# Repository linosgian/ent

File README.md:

# Ent

## Ergogen generated split keyboard

This fork of [ergogen](https://github.com/linosgian/ergogen/tree/lgian/custom_footprints) is used, which contains all the custom footprints that appear on the board (holes, trackpad, elite-c etc)

left | right
-|-
 | 

## Features

* Support for a [cirque](https://keycapsss.com/keyboard-parts/parts/211/glidepoint-cirque-trackpad-tm040040-tm035035?c=11) and [Azoteq](https://keycapsss.com/keyboard-parts/parts/247/azoteq-proxsense-i2c-touch-sensor-module/capacitive-trackpad) trackpads on the right side (solderable jumpers)
* Support for a rotary encoder on the left side (solderable jumpers)
* Uses elite-c (or equivalent like puchi-c) so more io pins are available
* No diodes (less complexity during soldering)
* Reversible
* Only supports choc v1

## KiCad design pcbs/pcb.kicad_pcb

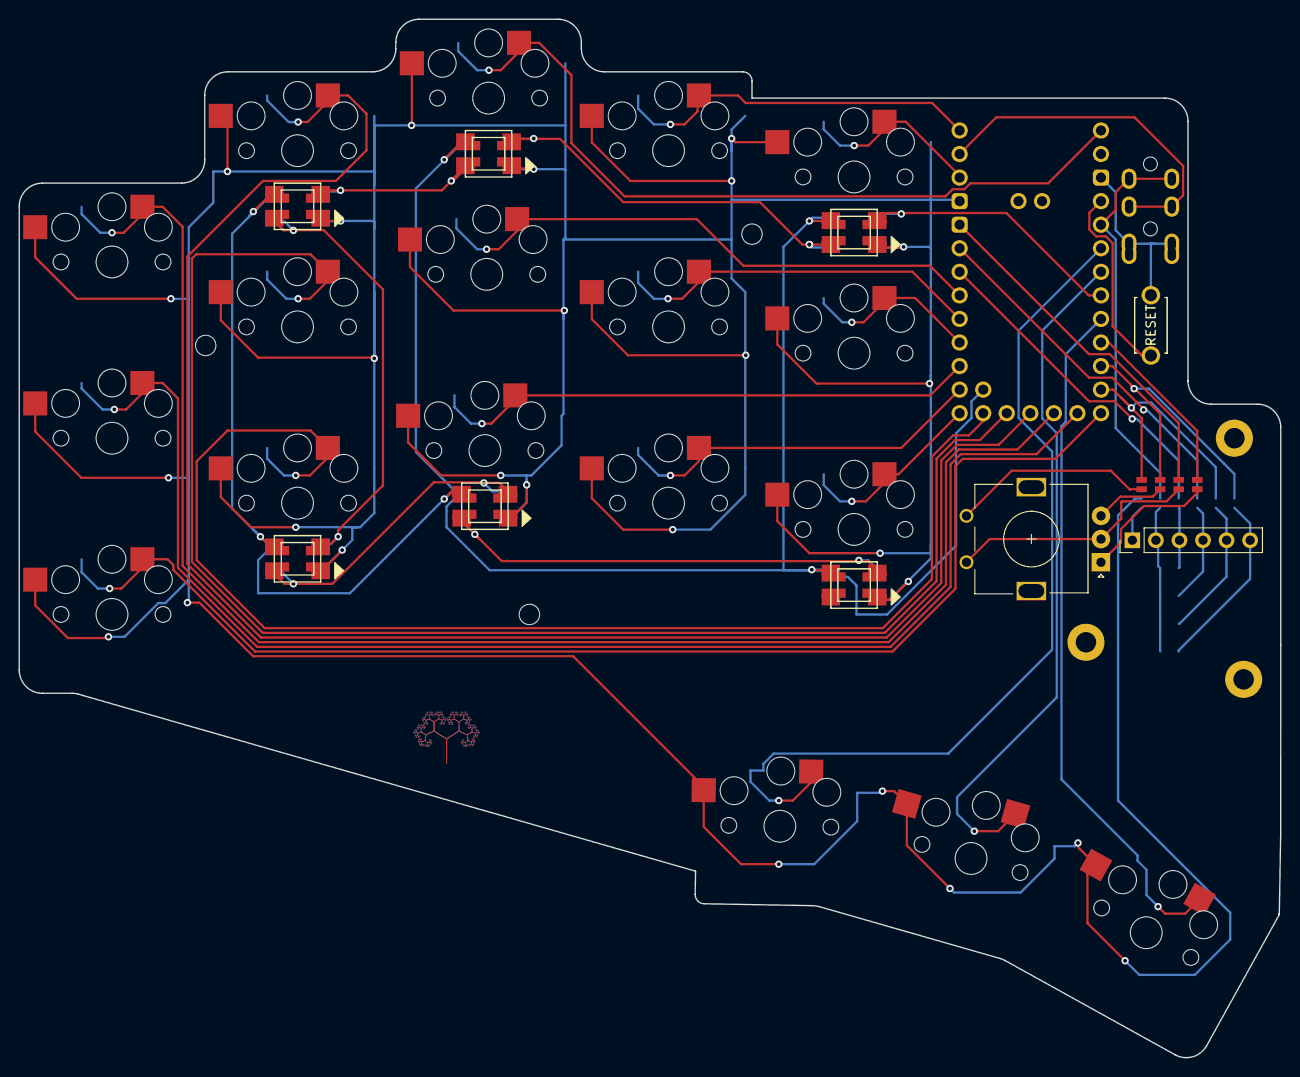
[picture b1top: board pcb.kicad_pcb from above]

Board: 2 copper layers, 136.0 x 112.0 mm, 50 parts (0 on the bottom side), 39 nets.

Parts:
J1, J2, J3, J4, J5, J6, J7, J8, J9, J10: Jumper
LED1, LED2, LED3, LED4, LED5, LED6, LED7, LED8, LED9, LED10, LED11, LED12: WS2812B
MCU1: Elite-C; Helios
ROT1: rotary_encoder
S1, S2, S3, S4, S5, S6, S7, S8, S9, S10, S11, S12, S13, S14, S15, S16, S17, S18: PG1350
TRRS1: TRRS-PJ-320A-dual
_1: ResetSW
_2, _3, _4: MountingHole_2.2mm_M2_Pad_Via
_5, _6, _7: MountingHole_2.2mm_M2

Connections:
A0: MCU1.23, S18.1
A1: LED5.4, LED5.44, LED11.4, LED11.44, MCU1.24
A2: MCU1.25, S17.1
A3: MCU1.26, S16.1
GND: J3.2, J5.2, LED1.3, LED1.33, LED2.3, LED2.33, LED3.3, LED3.33, LED4.3, LED4.33, LED5.3, LED5.33, LED6.3, LED6.33, LED7.3, LED7.33, LED8.3, LED8.33, LED9.3, LED9.33, LED10.3, LED10.33, LED11.3, LED11.33, LED12.3, LED12.33, MCU1.4, MCU1.5, MCU1.29, S1.2, S2.2, S3.2, S4.2, S5.2, S6.2, S7.2, S8.2, S9.2, S10.2, S11.2, S12.2, S13.2, S14.2, S15.2, S16.2, S17.2, S18.2, TRRS1.1, TRRS1.2, _1.2
IO2: J8.2, MCU1.6
IO3: J7.2, MCU1.7
IO4: MCU1.8, S8.1
IO5: MCU1.9, S11.1
IO6: MCU1.10, S14.1
IO7: MCU1.11, S7.1
IO8: MCU1.12, S10.1
IO9: MCU1.13, S13.1
IO10: MCU1.1, S12.1
IO11: MCU1.31, S9.1
IO12: MCU1.14, S4.1
IO13: MCU1.15, S5.1
IO14: MCU1.16, S6.1
IO15: MCU1.17, S3.1
IO16: MCU1.18, S2.1
IO20: J2.2, J10.2, MCU1.21
IO21: MCU1.19, S1.1
IO22: J4.2, MCU1.22
IO23: J1.2, J9.2, MCU1.20
NAN: LED6.2, LED6.22, LED12.2, LED12.22
O2: J1.1, ROT1.2
O3: J4.1, ROT1.A
O4: J3.1, ROT1.1, ROT1.C
O5: J2.1, ROT1.B
RGB: LED1.1, LED1.11, LED2.1, LED2.11, LED3.1, LED3.11, LED4.1, LED4.11, LED5.1, LED5.11, LED6.1, LED6.11, LED7.1, LED7.11, LED8.1, LED8.11, LED9.1, LED9.11, LED10.1, LED10.11, LED11.1, LED11.11, LED12.1, LED12.11, MCU1.32
RGB1: LED3.4, LED3.44, LED5.2, LED5.22, LED9.4, LED9.44, LED11.2, LED11.22
RGB2: LED1.4, LED1.44, LED3.2, LED3.22, LED7.4, LED7.44, LED9.2, LED9.22
RGB3: LED1.2, LED1.22, LED2.4, LED2.44, LED7.2, LED7.22, LED8.4, LED8.44
RGB4: LED2.2, LED2.22, LED4.4, LED4.44, LED8.2, LED8.22, LED10.4, LED10.44
RGB5: LED4.2, LED4.22, LED6.4, LED6.44, LED10.2, LED10.22, LED12.4, LED12.44
RST: MCU1.28, _1.1
RX: MCU1.3, S15.1
TX: MCU1.2, TRRS1.3
VCC: J6.2, MCU1.27, TRRS1.4

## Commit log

2023-05-12 Add README.md
2023-05-13 Add logo footprints
2023-05-14 Move a few IO pins around to enable I2C and TRRS communication
    Previously the wrong pins were used so TRRS and I2C (for cirque)
    wouldn't work. Thanks to (0), I didn't print the previous version of the
    board because nothing would work essentially.
    (0): https://www.reddit.com/r/ErgoMechKeyboards/comments/13ftrsc/comment/jjwuh69/?utm_source=reddit&utm_medium=web2x&context=3
2023-05-15 Moar fractals
2023-05-16 Finalize routing and logo
2023-05-17 Change logo
2023-05-17 Add fp-info-cache to .gitignore
2023-05-17 Update pcbdraw rendered images
2023-05-17 Add 3D printable bottom case with screw standoffs
2023-05-20 Convert to Helios (RP2040-based) MCU and add underglow LEDs
2023-05-20 Fix via overlapping with pad
2023-05-20 Re-generate gerber files
2023-05-21 Connect LEDs' VDD pin to Helios' RGB pin for stable 5V
2023-05-22 Update outlines and cases
2023-05-22 Add switchplane stl
2023-05-23 Add outline described by a polygon instead of using `bind`
2023-05-23 Move thumb cluster to the left by half a (choc) switch
2023-05-23 Reduce spread between keys in thumb cluster
2023-05-24 Fix thumb cluster spacing
2023-05-30 Remove pcb-backups
2023-05-30 Add support for azoteq TPS43 while maintaining support for cirque
2023-05-30 Re-run gerber file generation
2023-05-30 Recreate preview images
2023-05-31 Update README.md
    Add mention for Azoteq trackpad
2023-07-13 Add solid standoffs in the bottom plate
    Those will help in terms of stability for the thin 3D printed case
2023-07-14 Add a couple of standoffs near the MCU
2023-07-14 Cut out the bottom piece of the switchplate to reveal the PCB
2024-05-19 Make all TRRS cables compatible
